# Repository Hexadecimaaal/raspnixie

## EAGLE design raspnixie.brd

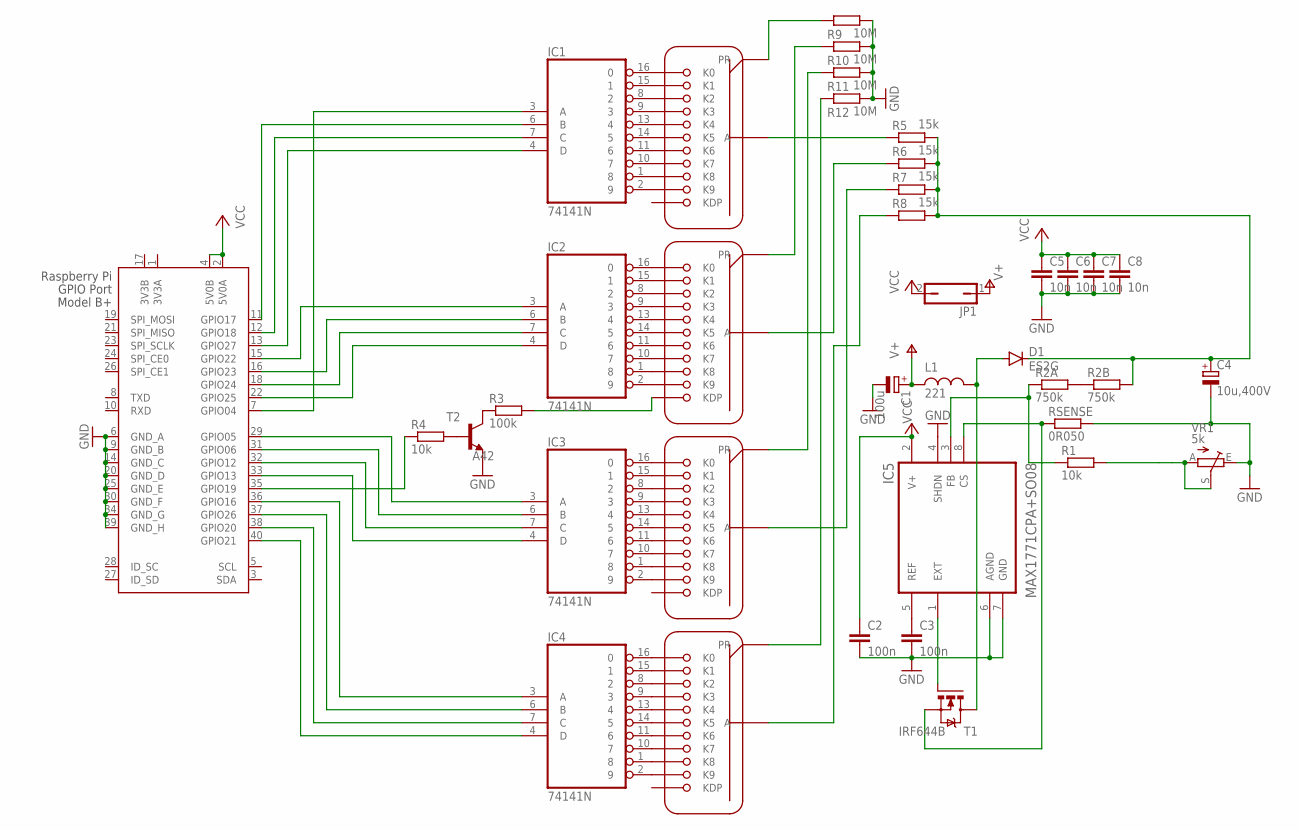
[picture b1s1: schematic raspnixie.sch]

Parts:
C1: 100u; CT7343
C2, C3: 100n; C1206K
C4: 10u,400V; E5-10,5
C5, C6, C7, C8: 10n; C1206K
D1: ES2G; DO214AA
IC1, IC2, IC3, IC4: 74141N; DIL16
IC5: MAX1771CPA+SO08; SO08
JP1: JP1Q; JP1
L1: 221; RESM175170X700N
R1, R4: 10k; R1206
R2A, R2B: 750k; R1206
R3: 100k; R1206
R5, R6, R7, R8: 15k; R1206
R9, R10, R11, R12: 10M; R1206
RSENSE: 0R050; R2010
T1: IRF644B; TO220BV
T2: A42; TO92
U1, U2, U3, U4: ZM1000
VR1: 5k; S64W-ROUND
X1: RASPI_BOARD_B+#_E3; RASPI_BOARD_B+_EDGES_3DRILL

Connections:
3V3A: X1.1 (3V3A)
3V3B: X1.17 (3V3B)
GND: C1.-, C2.2, C3.2, C4.-, C5.2, C6.2, C7.2, C8.2, IC1.12 (GND), IC2.12 (GND), IC3.12 (GND), IC4.12 (GND), IC5.4 (SHDN), IC5.6 (AGND), IC5.7 (GND), R9.2, R10.2, R11.2, R12.2, RSENSE.2, T2.1 (E), VR1.E, X1.6 (GND_A), X1.9 (GND_B), X1.14 (GND_C), X1.20 (GND_D), X1.25 (GND_E), X1.30 (GND_F), X1.34 (GND_G), X1.39 (GND_H)
unnamed: R9.1, U1.PR
unnamed: R10.1, U2.PR
unnamed: R11.1, U3.PR
unnamed: R12.1, U4.PR
unnamed: IC1.2 (9), U1.K9
unnamed: IC1.16 (0), U1.K0
unnamed: IC1.15 (1), U1.K8 (K1)
unnamed: IC1.8 (2), U1.K2
unnamed: IC1.9 (3), U1.K3
unnamed: IC1.13 (4), U1.K4
unnamed: IC1.14 (5), U1.K5
unnamed: IC1.11 (6), U1.K6
unnamed: IC1.10 (7), U1.K7
unnamed: IC1.1 (8), U1.K1 (K8)
unnamed: IC2.2 (9), U2.K9
unnamed: IC2.16 (0), U2.K0
unnamed: IC2.15 (1), U2.K8 (K1)
unnamed: IC2.8 (2), U2.K2
unnamed: IC2.9 (3), U2.K3
unnamed: IC2.13 (4), U2.K4
unnamed: IC2.14 (5), U2.K5
unnamed: IC2.11 (6), U2.K6
unnamed: IC2.10 (7), U2.K7
unnamed: IC2.1 (8), U2.K1 (K8)
unnamed: IC3.2 (9), U3.K9
unnamed: IC3.16 (0), U3.K0
unnamed: IC3.15 (1), U3.K8 (K1)
unnamed: IC3.8 (2), U3.K2
unnamed: IC3.9 (3), U3.K3
unnamed: IC3.13 (4), U3.K4
unnamed: IC3.14 (5), U3.K5
unnamed: IC3.11 (6), U3.K6
unnamed: IC3.10 (7), U3.K7
unnamed: IC3.1 (8), U3.K1 (K8)
unnamed: IC4.2 (9), U4.K9
unnamed: IC4.16 (0), U4.K0
unnamed: IC4.15 (1), U4.K8 (K1)
unnamed: IC4.8 (2), U4.K2
unnamed: IC4.9 (3), U4.K3
unnamed: IC4.13 (4), U4.K4
unnamed: IC4.14 (5), U4.K5
unnamed: IC4.11 (6), U4.K6
unnamed: IC4.10 (7), U4.K7
unnamed: IC4.1 (8), U4.K1 (K8)
unnamed: IC1.3 (A), X1.7 (GPIO04)
unnamed: IC1.6 (B), X1.11 (GPIO17)
unnamed: IC1.7 (C), X1.12 (GPIO18)
unnamed: IC1.4 (D), X1.13 (GPIO27)
unnamed: C3.1, IC5.5 (REF)
unnamed: IC2.6 (B), X1.16 (GPIO23)
unnamed: IC2.7 (C), X1.18 (GPIO24)
unnamed: IC2.4 (D), X1.22 (GPIO25)
unnamed: IC3.3 (A), X1.29 (GPIO05)
unnamed: IC3.6 (B), X1.31 (GPIO06)
unnamed: IC3.7 (C), X1.32 (GPIO12)
unnamed: IC3.4 (D), X1.33 (GPIO13)
unnamed: IC4.3 (A), X1.36 (GPIO16)
unnamed: IC4.6 (B), X1.37 (GPIO26)
unnamed: IC4.7 (C), X1.38 (GPIO20)
unnamed: IC4.4 (D), X1.40 (GPIO21)
unnamed: IC5.1 (EXT), T1.G
unnamed: D1.A, L1.2, T1.D
unnamed: IC5.8 (CS), RSENSE.1, T1.S
unnamed: IC2.3 (A), X1.15 (GPIO22)
unnamed: R5.1, U1.A1 (A), U1.A2 (A)
unnamed: R6.1, U2.A1 (A), U2.A2 (A)
unnamed: R4.2, T2.2 (B)
unnamed: R3.1, T2.3 (C)
unnamed: R1.2, VR1.A, VR1.S
unnamed: IC5.3 (FB), R1.1, R2A.1
unnamed: R7.1, U3.A1 (A), U3.A2 (A)
unnamed: R8.1, U4.A1 (A), U4.A2 (A)
unnamed: R4.1, X1.35 (GPIO19)
unnamed: R3.2, U2.KDP
unnamed: R2A.2, R2B.1
V+: C1.+, JP1.1, L1.1
VCC: C2.1, C5.1, C6.1, C7.1, C8.1, IC1.5 (VCC), IC2.5 (VCC), IC3.5 (VCC), IC4.5 (VCC), IC5.2 (V+), JP1.2, X1.2 (5V0A), X1.4 (5V0B)
VH: C4.+, D1.C, R2B.2, R5.2, R6.2, R7.2, R8.2

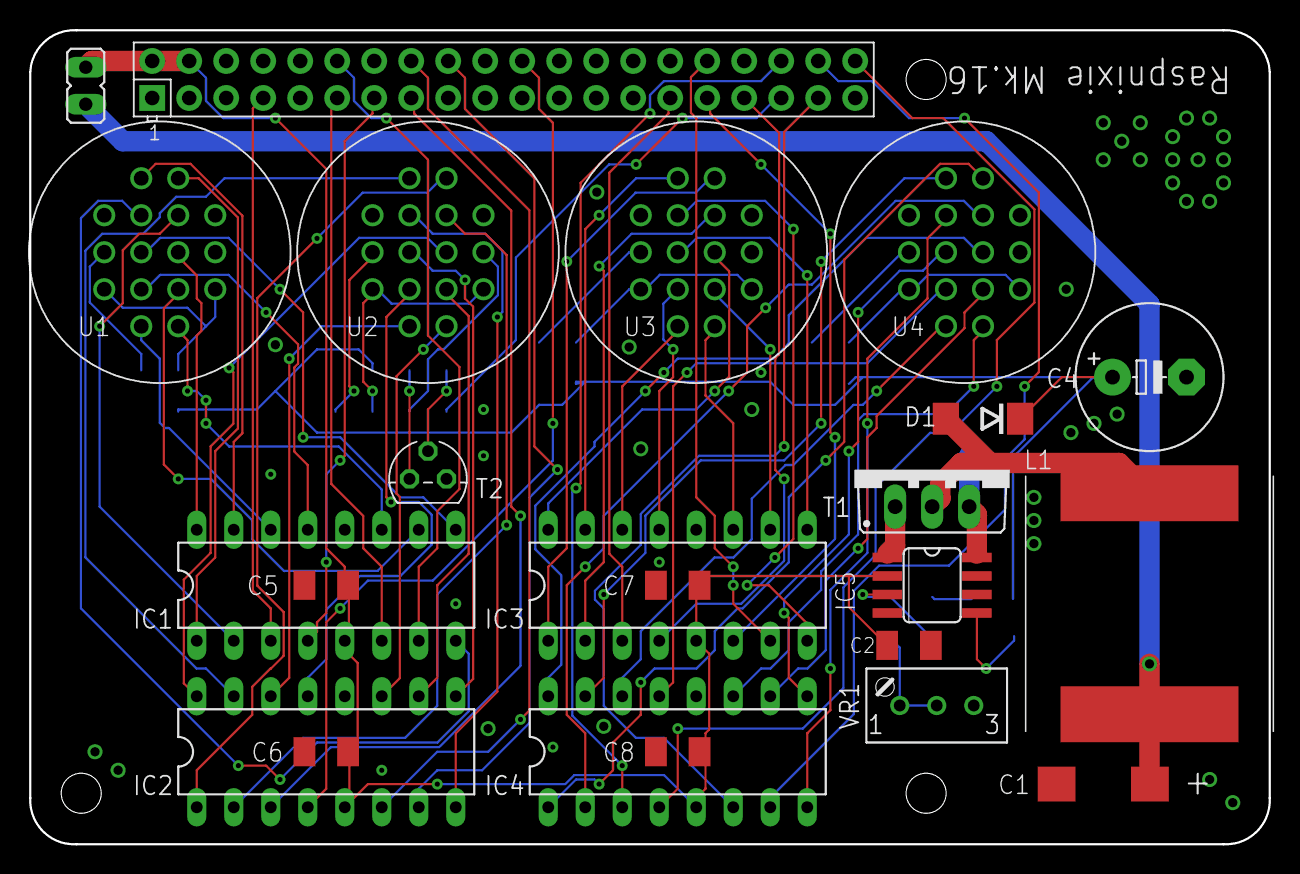
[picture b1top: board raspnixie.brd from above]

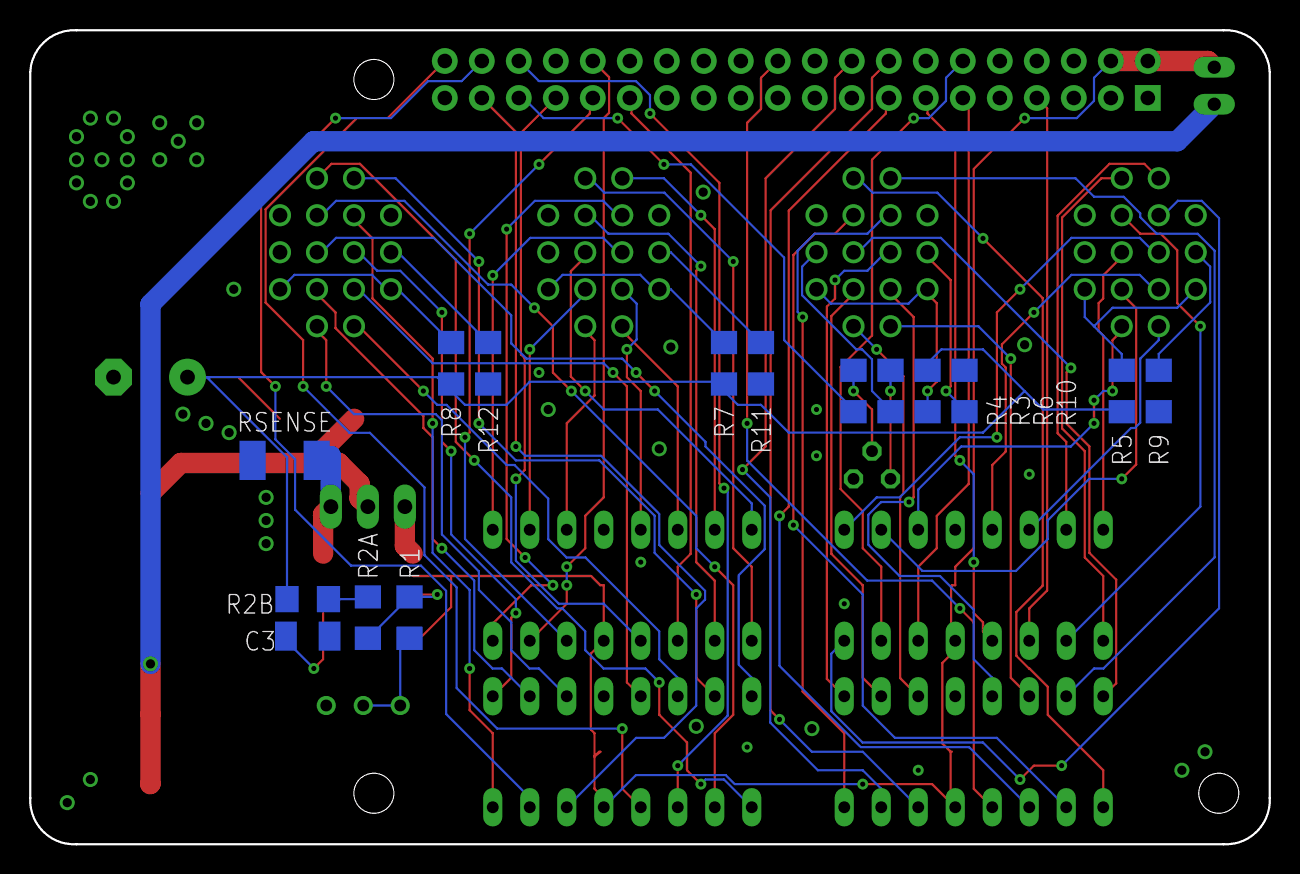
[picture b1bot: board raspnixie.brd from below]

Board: 2 copper layers, 85.1 x 55.9 mm, 38 parts (15 on the bottom side), 79 nets.

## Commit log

2020-04-02 mark. 14
2020-04-02 steal from other libraries
2021-06-07 2021-06-07 Mk.16
